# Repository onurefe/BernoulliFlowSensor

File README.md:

# BernoulliFlowSensor
Measuring phase shifts occurs during transmitting sound, this device determines local gas velocity vector at very high rates such as 1KHz.

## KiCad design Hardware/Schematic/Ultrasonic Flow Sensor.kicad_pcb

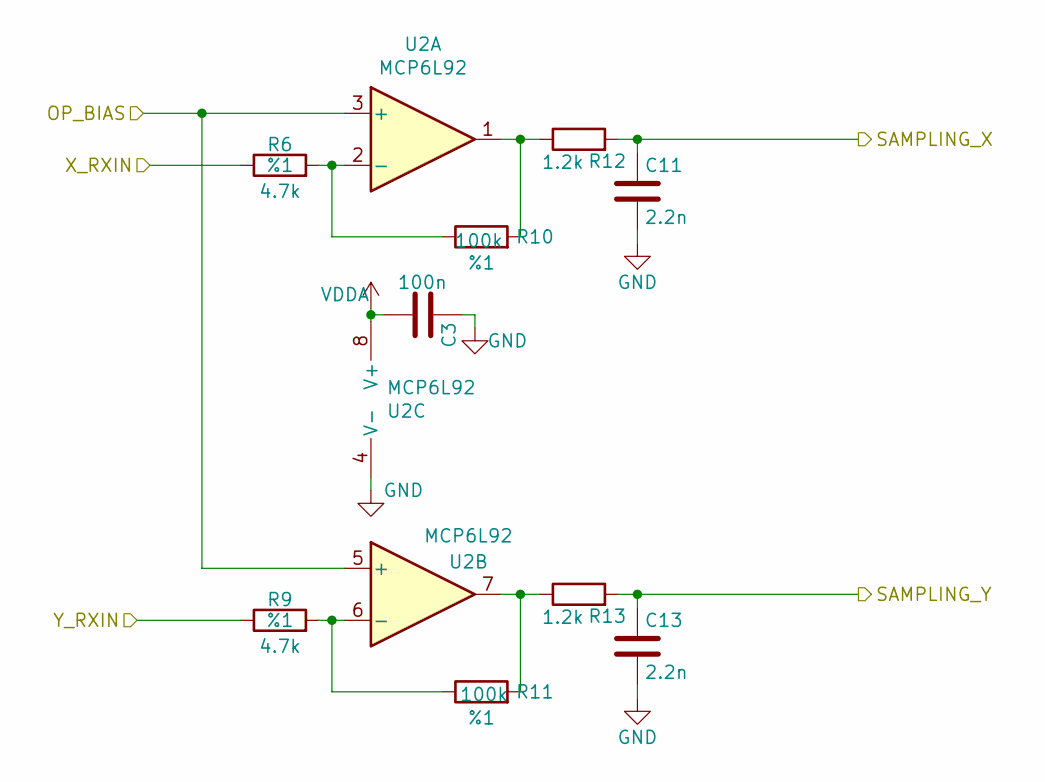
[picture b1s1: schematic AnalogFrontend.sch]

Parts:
C3: 100n; C_0603_1608Metric
C11, C13: 2.2n; C_0603_1608Metric
R6, R9: 4.7k; R_0603_1608Metric; Tolerance %1
R10, R11: 100k; R_0603_1608Metric; Tolerance %1
R12, R13: 1.2k; R_0603_1608Metric
U2: MCP6L92; SOIC-8_3.9x4.9mm_P1.27mm

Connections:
/OP_BIAS: U2.3 (+), U2.5 (+); also elsewhere on the board
/RX_X: R6.1; also elsewhere on the board
/RX_Y: R9.1; also elsewhere on the board
/SAMPLING_X: C11.1, R12.2; also elsewhere on the board
/SAMPLING_Y: C13.1, R13.2; also elsewhere on the board
GND: C3.1, C11.2, C13.2, U2.4 (V-); also elsewhere on the board
unnamed: R6.2, R10.1, U2.2 (-)
unnamed: R10.2, R12.1, U2.1
unnamed: R9.2, R11.1, U2.6 (-)
unnamed: R11.2, R13.1, U2.7
VDDA: C3.2, U2.8 (V+); also elsewhere on the board

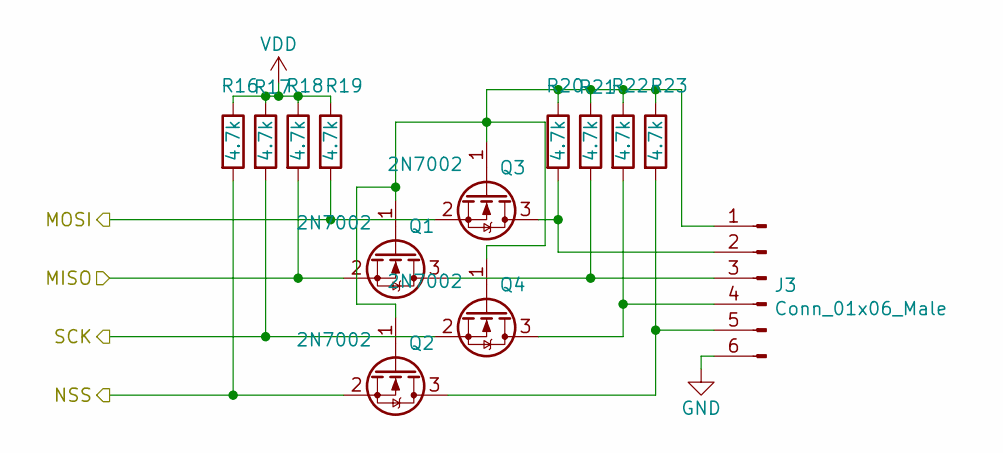
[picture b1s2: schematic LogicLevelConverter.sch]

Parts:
J3: Conn_01x06_Male; PinHeader_1x06_P2.54mm_Vertical
Q1, Q2, Q3, Q4: 2N7002; SOT-23
R16, R17, R18, R19, R20, R21, R22, R23: 4.7k; R_0603_1608Metric

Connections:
/MISO: Q1.2 (S), R18.2; also elsewhere on the board
/MOSI: Q3.2 (S), R19.2; also elsewhere on the board
/NSS: Q2.2 (S), R16.2; also elsewhere on the board
/SCK: Q4.2 (S), R17.2; also elsewhere on the board
GND: J3.6; also elsewhere on the board
unnamed: J3.1, Q1.1 (G), Q2.1 (G), Q3.1 (G), Q4.1 (G), R20.1, R21.1, R22.1, R23.1
unnamed: J3.2, Q3.3 (D), R20.2
unnamed: J3.3, Q1.3 (D), R21.2
unnamed: J3.4, Q4.3 (D), R22.2
unnamed: J3.5, Q2.3 (D), R23.2
VDD: R16.1, R17.1, R18.1, R19.1; also elsewhere on the board

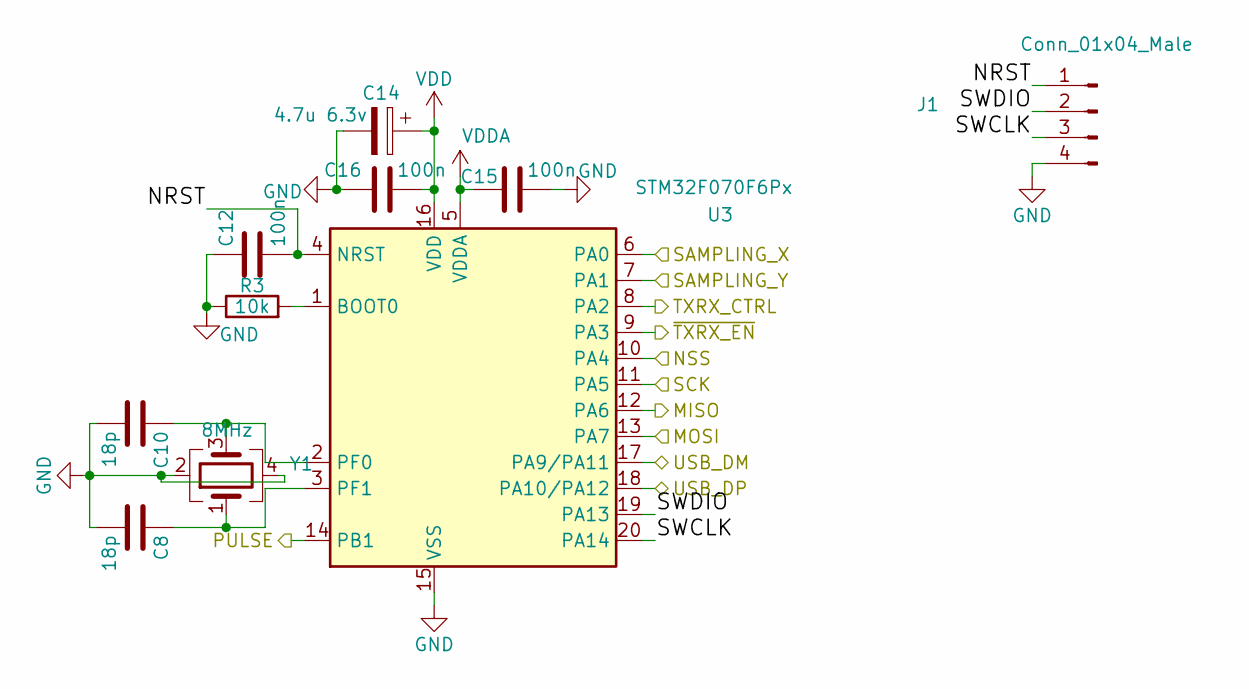
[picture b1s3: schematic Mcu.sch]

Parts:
C8, C10: 18p; C_0603_1608Metric
C12, C15, C16: 100n; C_0603_1608Metric
C14: 4.7u 6.3v; C_1206_3216Metric
J1: Conn_01x04_Male; PinHeader_1x04_P2.54mm_Vertical
R3: 10k; R_0603_1608Metric
U3: STM32F070F6Px; TSSOP-20_4.4x6.5mm_P0.65mm
Y1: 8MHz; Crystal_5x3.2mm_4leads

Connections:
/MISO: U3.12 (PA6); also elsewhere on the board
/MOSI: U3.13 (PA7); also elsewhere on the board
/Mcu/NRST: C12.2, J1.1, U3.4 (NRST)
/Mcu/SWCLK: J1.3, U3.20 (PA14)
/Mcu/SWDIO: J1.2, U3.19 (PA13)
/NSS: U3.10 (PA4); also elsewhere on the board
/PULSE: U3.14 (PB1); also elsewhere on the board
/SAMPLING_X: U3.6 (PA0); also elsewhere on the board
/SAMPLING_Y: U3.7 (PA1); also elsewhere on the board
/SCK: U3.11 (PA5); also elsewhere on the board
/TXRX_CTRL: U3.8 (PA2); also elsewhere on the board
/USB_DM: U3.17 (PA9/PA11); also elsewhere on the board
/USB_DP: U3.18 (PA10/PA12); also elsewhere on the board
/~TXRX_EN: U3.9 (PA3); also elsewhere on the board
GND: C8.2, C10.2, C12.1, C14.2, C15.2, C16.1, J1.4, R3.1, U3.15 (VSS), Y1.2, Y1.4; also elsewhere on the board
unnamed: C8.1, U3.3 (PF1), Y1.1
unnamed: C10.1, U3.2 (PF0), Y1.3
unnamed: R3.2, U3.1 (BOOT0)
VDD: C14.1, C16.2, U3.16 (VDD); also elsewhere on the board
VDDA: C15.1, U3.5 (VDDA); also elsewhere on the board

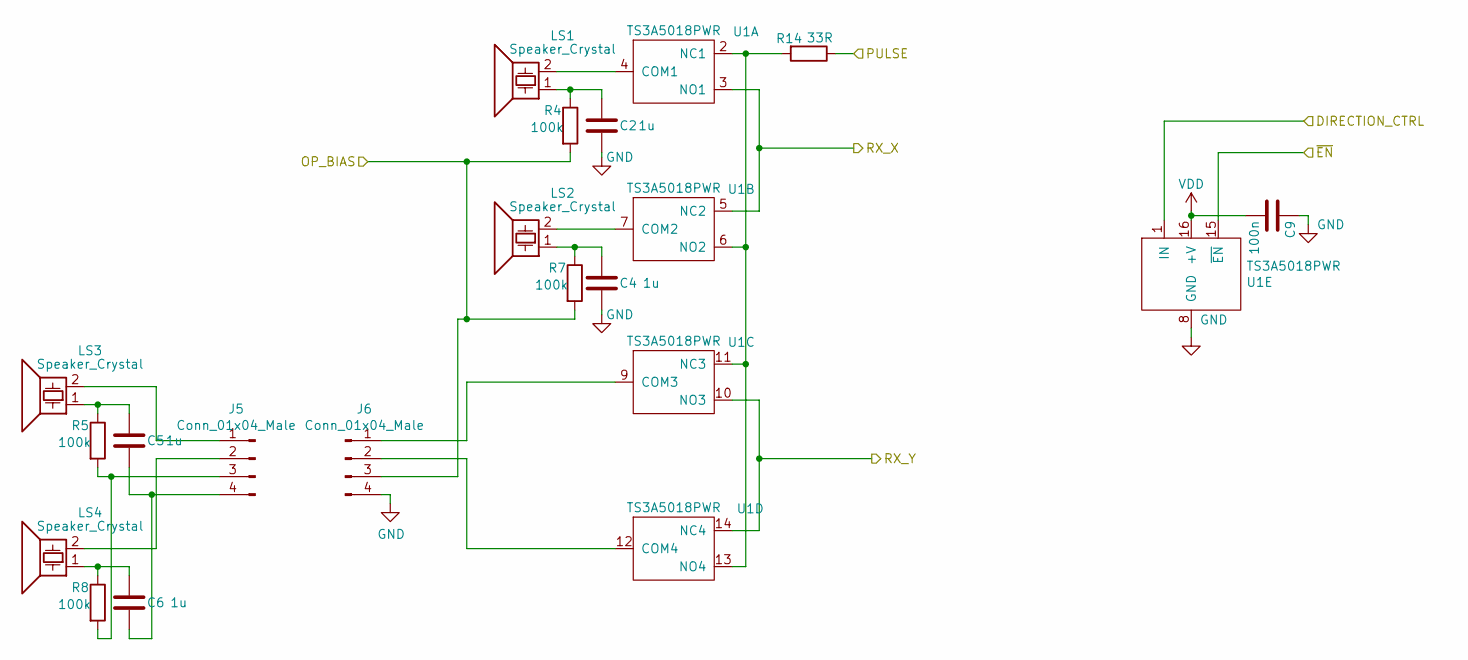
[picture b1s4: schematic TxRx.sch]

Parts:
C2, C4, C5, C6: 1u; C_0603_1608Metric
C9: 100n; C_0603_1608Metric
J5, J6: Conn_01x04_Male; JST_EH_B4B-EH-A_1x04_P2.50mm_Vertical
LS1, LS2, LS3, LS4: Speaker_Crystal; ultrasound_piezo_round_D10mmxP6mm
R4, R5, R7, R8: 100k; R_0603_1608Metric
R14: 33R; R_0603_1608Metric
U1: TS3A5018PWR; TSSOP-16_4.4x5mm_P0.65mm

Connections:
/OP_BIAS: J6.3, R4.2, R7.2; also elsewhere on the board
/PULSE: R14.1; also elsewhere on the board
/RX_X: U1.3 (NO1), U1.5 (NC2); also elsewhere on the board
/RX_Y: U1.10 (NO3), U1.14 (NC4); also elsewhere on the board
/TXRX_CTRL: U1.1 (IN); also elsewhere on the board
/~TXRX_EN: U1.15 (~EN); also elsewhere on the board
GND: C2.2, C4.2, C9.1, J6.4, U1.8 (GND); also elsewhere on the board
unnamed: C2.1, LS1.1, R4.1
unnamed: C4.1, LS2.1, R7.1
unnamed: C5.1, LS3.1, R5.1
unnamed: C5.2, C6.2, J5.4
unnamed: C6.1, LS4.1, R8.1
unnamed: J5.1, LS3.2
unnamed: J5.2, LS4.2
unnamed: J5.3, R5.2, R8.2
unnamed: J6.1, U1.9 (COM3)
unnamed: J6.2, U1.12 (COM4)
unnamed: LS1.2, U1.4 (COM1)
unnamed: LS2.2, U1.7 (COM2)
unnamed: R14.2, U1.2 (NC1), U1.6 (NO2), U1.11 (NC3), U1.13 (NO4)
VDD: C9.2, U1.16 (+V); also elsewhere on the board

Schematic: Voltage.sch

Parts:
C1, C18, C20: 100n; C_0603_1608Metric
C7, C17, C22: 1u; C_0603_1608Metric
J4: Conn_01x02_Male; PinHeader_1x02_P2.54mm_Vertical
R1, R2: 4.7k; R_0603_1608Metric; Tolerance %1
U4, U5: MIC5504-3.3YM5; SOT-23-5

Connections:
+5V: C18.2, C20.2, J4.1, U4.1 (VIN), U4.3 (EN), U5.1 (VIN), U5.3 (EN); also elsewhere on the board
/OP_BIAS: C1.1, C7.1, R1.2, R2.1; also elsewhere on the board
GND: C1.2, C7.2, C17.2, C18.1, C20.1, C22.2, J4.2, R2.2, U4.2 (GND), U5.2 (GND); also elsewhere on the board
VDD: C22.1, U4.5 (VOUT); also elsewhere on the board
VDDA: C17.1, R1.1, U5.5 (VOUT); also elsewhere on the board

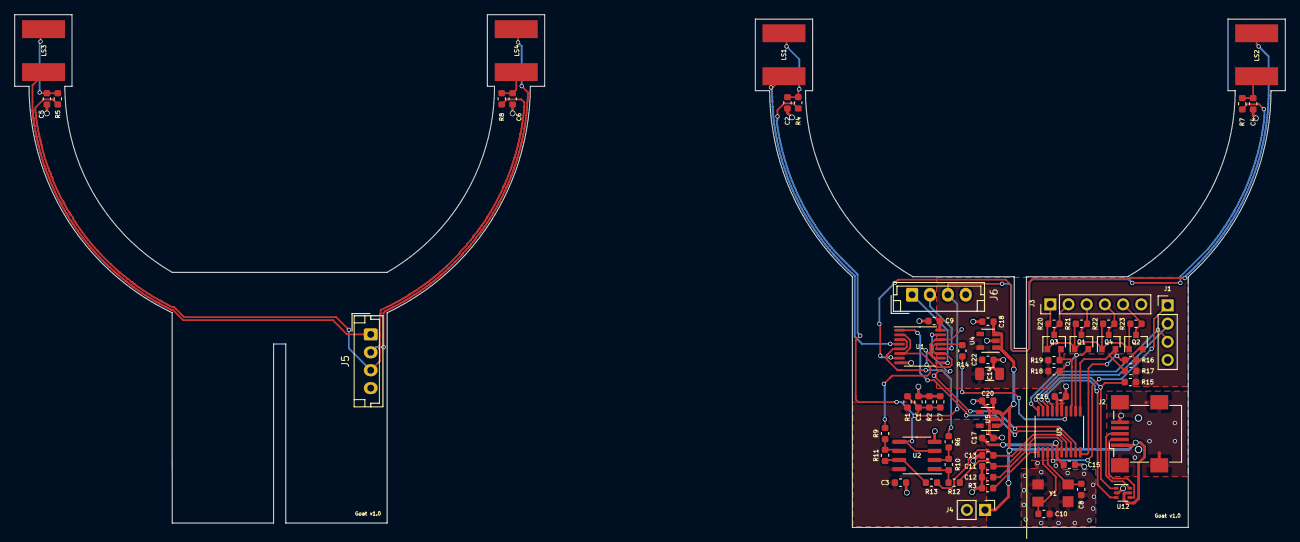
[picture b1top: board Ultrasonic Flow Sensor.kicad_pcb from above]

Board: 2 copper layers, 177.4 x 71.6 mm, 64 parts (0 on the bottom side), 48 nets.

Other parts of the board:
J2: USB_B_Mini; USB_Mini-B_Wuerth_65100516121_Horizontal
R15: 1.5k; R_0603_1608Metric
U12: NUF2221W6; SOT-363_SC-70-6

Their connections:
+5V: J2.1 (VBUS), U12.5 (VBUS); also elsewhere on the board
/USB_DM: U12.3 (D2i); also elsewhere on the board
/USB_DP: R15.2, U12.1 (D1i); also elsewhere on the board
GND: J2.5 (GND), J2.6 (Shield), U12.2 (GND); also elsewhere on the board
unnamed: J2.2 (D-), U12.4 (D2c)
unnamed: J2.3 (D+), U12.6 (D1c)
VDD: R15.1; also elsewhere on the board

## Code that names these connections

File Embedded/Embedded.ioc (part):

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Mcu.Name=STM32F070F6Px
Mcu.Package=TSSOP20
Mcu.UserName=STM32F070F6Px
PA0.GPIOParameters=GPIO_Label
PA0.GPIO_Label=SAMPLING_X
PA0.Mode=IN0
PA0.Signal=ADC_IN0
PA1.GPIOParameters=GPIO_Label
PA1.GPIO_Label=SAMPLING_Y
PA1.Mode=IN1
PA1.Signal=ADC_IN1
PA11.Mode=Device
PA11.Signal=USB_DM
PA12.Mode=Device
PA12.Signal=USB_DP
PA13.GPIOParameters=GPIO_Label
PA13.GPIO_Label=SWDIO
PA13.Mode=Serial_Wire
PA13.Signal=SYS_SWDIO
PA14.GPIOParameters=GPIO_Label
PA14.GPIO_Label=SWCLK
PA14.Mode=Serial_Wire
PA14.Signal=SYS_SWCLK
PA2.GPIOParameters=GPIO_Label
PA2.GPIO_Label=TXRX_CTRL
PA2.Signal=GPIO_Output
PA3.GPIOParameters=PinState,GPIO_Label
PA3.GPIO_Label=TXRX_nEN
PA3.PinState=GPIO_PIN_SET
PA3.Signal=GPIO_Output
PA4.GPIOParameters=GPIO_Label
PA4.GPIO_Label=NSS
PA4.Mode=NSS_Signal_Hard_Input
PA4.Signal=SPI1_NSS
PA5.GPIOParameters=GPIO_Label
PA5.GPIO_Label=SCK
PA5.Mode=Full_Duplex_Slave
PA5.Signal=SPI1_SCK
PA6.GPIOParameters=GPIO_Label
PA6.GPIO_Label=MISO
PA6.Mode=Full_Duplex_Slave
PA6.Signal=SPI1_MISO
PA7.GPIOParameters=GPIO_Label
PA7.GPIO_Label=MOSI
PA7.Mode=Full_Duplex_Slave
PA7.Signal=SPI1_MOSI
PB1.GPIOParameters=GPIO_Label
PB1.GPIO_Label=PULSE
PB1.Mode=Output Compare3 CH3N
PB1.Signal=TIM1_CH3N
PF0-OSC_IN.Mode=HSE-External-Oscillator
PF0-OSC_IN.Signal=RCC_OSC_IN
PF1-OSC_OUT.Mode=HSE-External-Oscillator
PF1-OSC_OUT.Signal=RCC_OSC_OUT
RCC.SYSCLKFreq_VALUE=48000000
RCC.SYSCLKSource=RCC_SYSCLKSOURCE_PLLCLK
board=custom

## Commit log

2020-06-06 Hardware and firmware components written, not tested.
2020-09-02 Kicad v5 files added.
